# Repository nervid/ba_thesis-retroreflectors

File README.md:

# ba_thesis-retroreflectors
RF-Retroreflectors: The Use of Backscatter in Short Range Communication

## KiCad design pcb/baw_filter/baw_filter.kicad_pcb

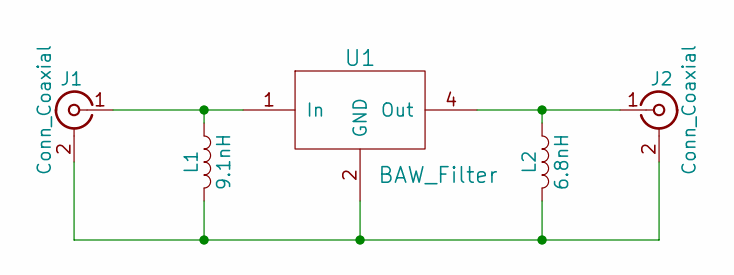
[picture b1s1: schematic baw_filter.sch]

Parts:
J1, J2: Conn_Coaxial; Molex_SMA_Jack_Edge_Mount
L1: 9.1nH; L_0603
L2: 6.8nH; L_0603
U1: BAW_Filter; 885062

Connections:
GND: J1.2 (Ext), J2.2 (Ext), L1.2, L2.2, U1.2 (GND), U1.3 (GND), U1.5 (GND)
unnamed: J1.1 (In), L1.1, U1.1 (In)
unnamed: J2.1 (In), L2.1, U1.4 (Out)

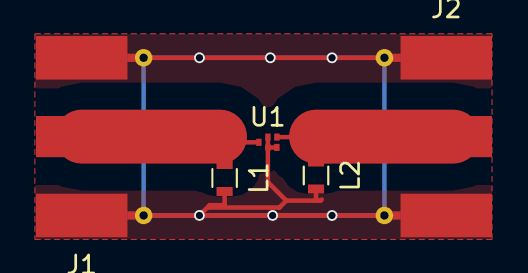
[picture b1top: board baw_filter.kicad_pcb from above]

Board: 2 copper layers, 5 parts (0 on the bottom side), 3 nets.

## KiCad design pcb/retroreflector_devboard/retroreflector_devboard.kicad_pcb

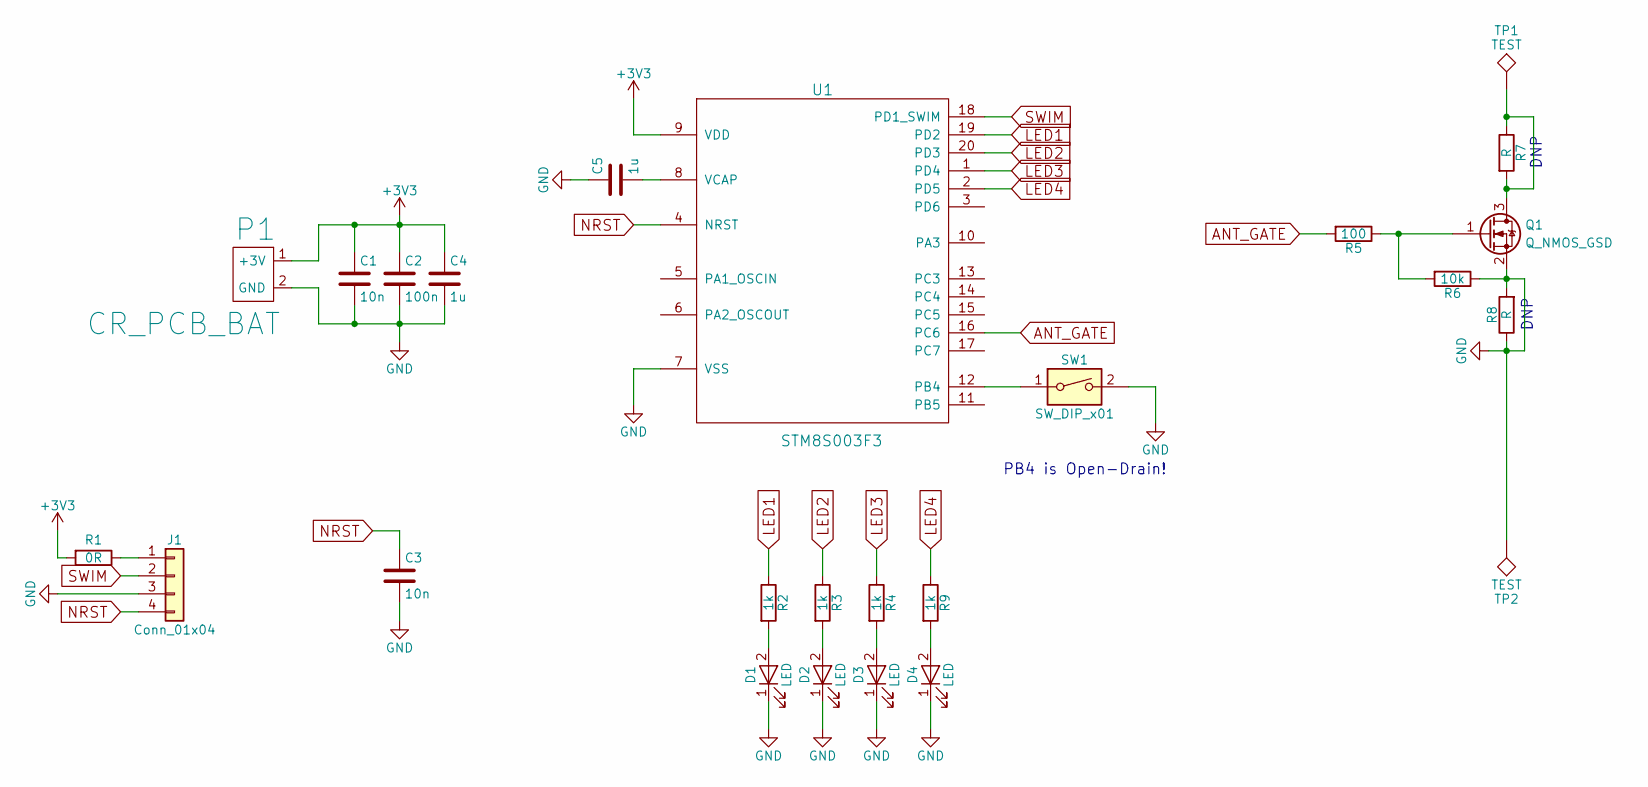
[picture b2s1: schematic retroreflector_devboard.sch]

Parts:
C1, C3: 10n; C_0603_HandSoldering
C2: 100n; C_0603_HandSoldering
C4, C5: 1u; C_0603_HandSoldering
D1, D2, D3, D4: LED; LED_0603_HandSoldering
J1: Conn_01x04; Pin_Header_Straight_1x04_Pitch2.54mm_SMD_Pin1Left
P1: CR_PCB_BAT; CR2032_PCB_BAT
Q1: Q_NMOS_GSD; SOT-23_Handsoldering
R1: 0R; R_0603_HandSoldering
R2, R3, R4, R9: 1k; R_0603_HandSoldering
R5: 100; R_0603_HandSoldering
R6: 10k; R_0603_HandSoldering
R7, R8: R; R_0603_HandSoldering
SW1: SW_DIP_x01; SW_DIP_x1_W8.61mm_Slide_LowProfile
TP1, TP2: TEST; SolderWirePad_single_SMD_5x10mm
U1: STM8S003F3; TSSOP-20_4.4x6.5mm_Pitch0.65mm

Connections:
+3V3: C1.1, C2.1, C4.1, P1.1 (+3V), R1.2, U1.9 (VDD)
ANT_GATE: R5.2, U1.16 (PC6)
GND: C1.2, C2.2, C3.2, C4.2, C5.1, D1.1 (K), D2.1 (K), D3.1 (K), D4.1 (K), J1.3, P1.2 (GND), Q1.2 (S), R6.1, R8.1, R8.2, SW1.2, TP2.1, U1.7 (VSS)
LED1: R2.1, U1.19 (PD2)
LED2: R3.1, U1.20 (PD3)
LED3: R4.1, U1.1 (PD4)
LED4: R9.1, U1.2 (PD5)
NRST: C3.1, J1.4, U1.4 (NRST)
unnamed: C5.2, U1.8 (VCAP)
unnamed: D1.2 (A), R2.2
unnamed: D2.2 (A), R3.2
unnamed: D3.2 (A), R4.2
unnamed: D4.2 (A), R9.2
unnamed: J1.1, R1.1
unnamed: Q1.1 (G), R5.1, R6.2
unnamed: Q1.3 (D), R7.1, R7.2, TP1.1
unnamed: SW1.1, U1.12 (PB4)
SWIM: J1.2, U1.18 (PD1_SWIM)

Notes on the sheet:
DNP
PB4 is Open-Drain!

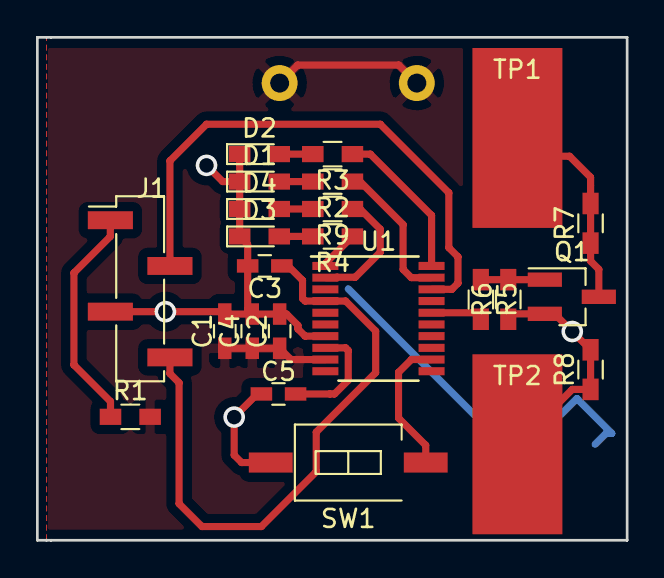
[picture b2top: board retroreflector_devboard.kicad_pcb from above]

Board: 2 copper layers, 32.8 x 27.9 mm, 25 parts (1 on the bottom side), 18 nets.

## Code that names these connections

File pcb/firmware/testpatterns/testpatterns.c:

#include "gpio.h"
#include "clk.h"
#include "spi.h"

#define LED1_PORT gpiod
#define LED1_PIN gpio_pin_3

#define LED2_PORT gpiod
#define LED2_PIN gpio_pin_2

#define LED3_PORT gpiod
#define LED3_PIN gpio_pin_5

#define LED4_PORT gpiod
#define LED4_PIN gpio_pin_4


#define BUTTON_PORT gpiob
#define BUTTON_PIN 4

#define MOSI_PORT gpioc
#define MOSI_PIN gpio_pin_6

typedef enum{
  pattern_mode_clk,
  pattern_mode_3byte,
  pattern_mode_2byte,
  pattern_mode_1byte

}pattern_mode_t;

void _delay_long(){
  unsigned long int x;

  for(x=0;x<50000;x++);
}

void _delay(){
  unsigned long int x;

  for(x=0;x<50;x++);
}

void display_mode(pattern_mode_t mode)
{
  uint8_t leds;

  leds = gpiod->odr & ~(0x1E); // blank leds
  
  switch(mode){
  case pattern_mode_clk:
    leds |= 1<<2;
    break;

  case pattern_mode_3byte:
    leds |= 1<<3;
    break;

  case pattern_mode_2byte:
    leds |= 1<<4;
    break;
    
  case pattern_mode_1byte:
    leds |= 1<<5;
    break;
    
  default:

    break;
  }

  LED1_PORT->odr = leds;
}

pattern_mode_t switch_mode(pattern_mode_t mode)
{
  //if(gpio_read(BUTTON_PORT, BUTTON_PIN) == 0){
  if((gpiob->idr & (1<<4)) == 0){
    switch(mode){
    case pattern_mode_clk:
      mode = pattern_mode_3byte;
      break;
    
    case pattern_mode_3byte:
      mode = pattern_mode_2byte;
      break;

    case pattern_mode_2byte:
      mode = pattern_mode_1byte;
      break;

    case pattern_mode_1byte:
      mode = pattern_mode_clk;
      break;

    default:
      mode = pattern_mode_clk;
      break;
    }
  }
  
  return mode;
}

void send_data(pattern_mode_t mode)
{
  //const uint8_t data[8] = {0xAA, 0xAA, 0xAA, 0x55, 0x55, 'T', 'E', 0x00};
  const uint8_t data[8] = {0xAA, 0xA7, 0x12, 'T', 'E', 'S', 'T', 0xAA};
  static data_cnt = 0;
  
  switch(mode){
  case pattern_mode_clk:
    //spi_txonly_start();
    spi_txonly_transmit(0xAA);
    break;

  case pattern_mode_3byte:
    spi_txonly_transmit(data[data_cnt]);
    data_cnt++;

    if(data_cnt > 7){
      data_cnt = 0;
      //_delay_long();
    }
    
  default:
    break;
  }

}


char calcCRC(char *data, int length)
{
  int crc = 0;
	int i, j;
	
	for(j=0; j < length; j++)
	{
		crc ^= (data[j] << 8);
		
		for(i=0;i<8;i++)
		{
			if((crc & 0x8000) != 0)
				crc ^= (0x1070 << 3);
		
			crc <<= 1;
		}
	}
	
	return (char)(crc >> 8);
} 


void send_frame(uint8_t *data, uint8_t id){
  uint8_t i, j;
  uint8_t frame[9] = {0xAA, 0xA7, 0x12}; // insert preamble
  frame[3] = id;
  
  for(i = 0; i<4; i++){
    frame[4+i] = data[i];
  }
  frame[8] = calcCRC(&frame[3],5); 

  for(j=0;j<10;j++){
    for(i = 0; i<9; i++){
      spi_txonly_transmit(frame[i]);
    }
  }
}


		  
int main(){
  unsigned long int cnt=0;
  pattern_mode_t mode = pattern_mode_3byte;

  uint8_t id = 0;
  const uint8_t data[4] = {'T', 'E', 'S', 'T'};
  // clk setup
  clk_set_source_auto(clk_source_hsi);
  clk_set_cpudiv(clk_cpudiv_1);
  clk_set_hsidiv(clk_hsidiv_8);


  // gpio setup
  gpio_mode(LED1_PORT,1<<2,gpio_mode_out_pp); // set up led pin as push-pull output
  gpio_mode(LED2_PORT,1<<3,gpio_mode_out_pp);
  gpio_mode(LED3_PORT,1<<4,gpio_mode_out_pp);
  gpio_mode(LED4_PORT,1<<5,gpio_mode_out_pp);

  gpio_mode(BUTTON_PORT,BUTTON_PIN,gpio_mode_in);
  
  gpio_mode(MOSI_PORT, MOSI_PIN, gpio_mode_out_pp);

  //spi_txonly_start();
  spi_txonly_start();
  while(1){


    
    //spi_txonly_transmit(0xAA);
    //gpio_toggle(LED_PORT,LED_PIN);

    //if((cnt % 10) == 0){
      //mode = switch_mode(mode);
      //display_mode(mode);
      id++;
      //}
    //send data here 
    //send_data(mode);
    
    //_delay();

    send_frame(data,id);
    
  }
}

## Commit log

2018-08-07 updated readme file with abstract
2018-08-07 missing line breaks
2019-04-15 added documentation
2019-04-15 added simulation
2019-04-15 added gnuradio stuff
2019-04-15 added pcb and firmware files
